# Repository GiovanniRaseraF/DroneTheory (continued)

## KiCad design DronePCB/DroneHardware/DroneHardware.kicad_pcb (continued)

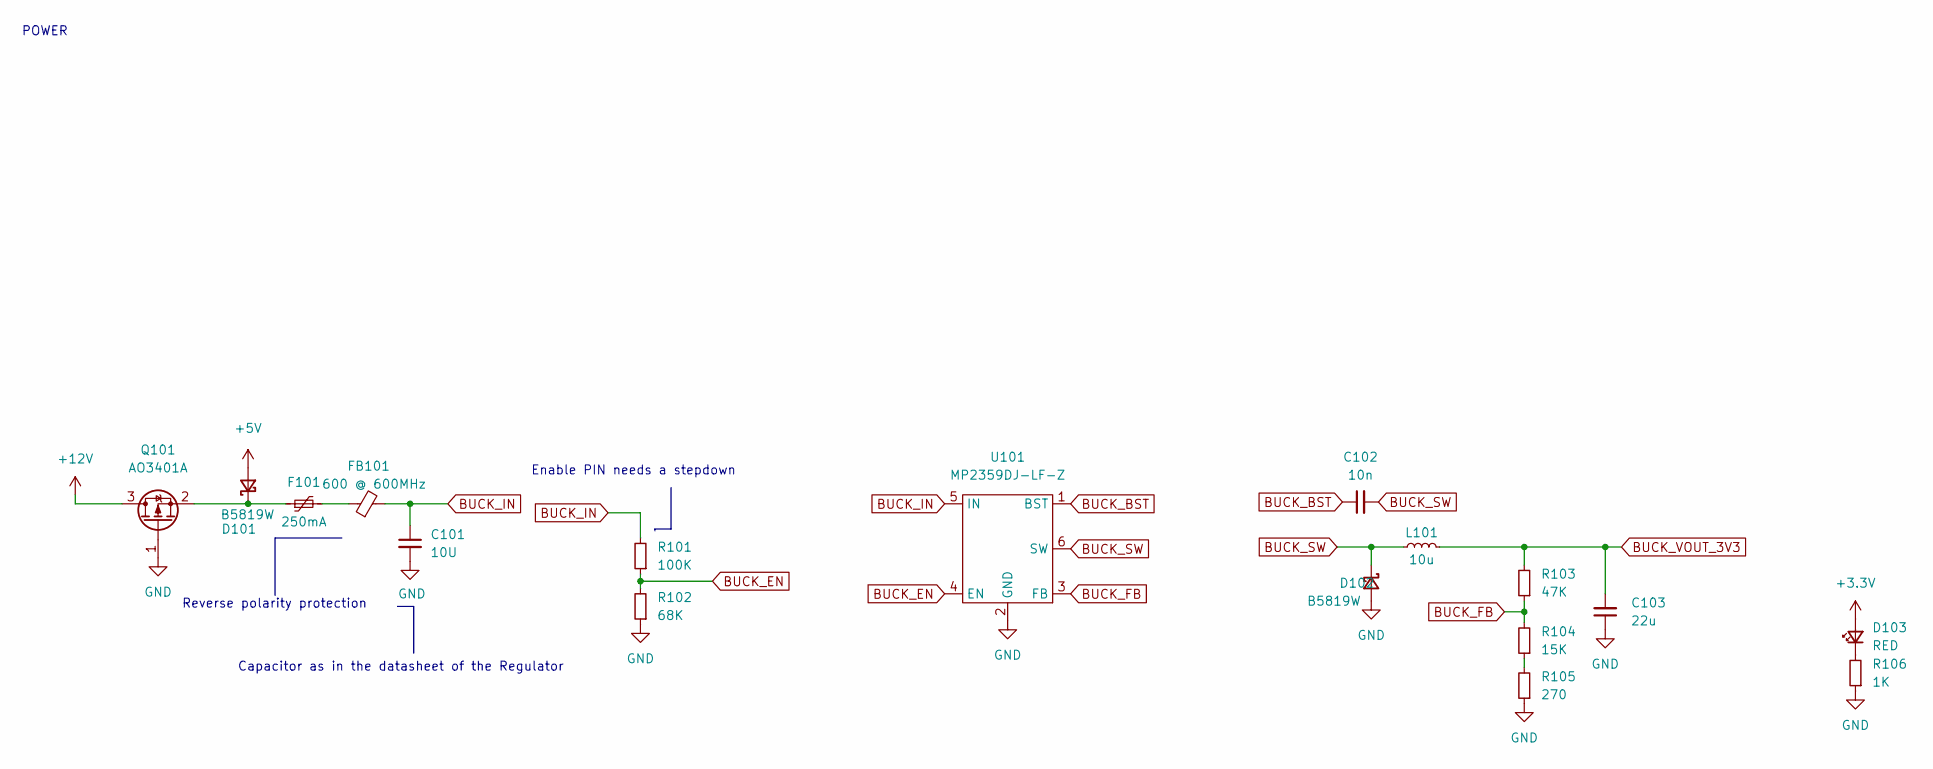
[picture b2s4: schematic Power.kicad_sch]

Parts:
C101: 10U; C_1206_3216Metric; LCSC Part # C13585
C102: 10n; C_0603_1608Metric; LCSC Part # C57112
C103: 22u; C_1206_3216Metric; LCSC Part # C12891
D101, D102: B5819W; D_SOD-123; LCSC Part # C8598
D103: RED; LED_0603_1608Metric; LCSC Part # C2286
F101: 250mA; Fuse_0603_1608Metric; LCSC Part # C151137
FB101: 600 @ 600MHz; L_0805_2012Metric; LCSC Part # C1017
L101: 10u; L_Sunlord_MWSA0518_5.4x5.2mm; LCSC Part # C139506
Q101: AO3401A; SOT-23; LCSC Part # C15127
R101: 100K; R_0603_1608Metric; LCSC Part # C25803
R102: 68K; R_0603_1608Metric; LCSC Part # C23231
R103: 47K; R_0603_1608Metric; LCSC Part # C25819
R104: 15K; R_0603_1608Metric; LCSC Part # C22809
R105: 270; R_0603_1608Metric; LCSC Part # C22966
R106: 1K; R_0603_1608Metric; LCSC Part # C21190
U101: MP2359DJ-LF-Z; SOT-23-6; LCSC Part # C14259

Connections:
+5V: D101.2 (A); also elsewhere on the board
+12V: Q101.3 (D); also elsewhere on the board
BUCK_BST: C102.1, U101.1 (BST)
BUCK_EN: R101.1, R102.2, U101.4 (EN)
BUCK_FB: R103.1, R104.2, U101.3 (FB)
BUCK_IN: C101.1, FB101.2, R101.2, U101.5 (IN)
BUCK_SW: C102.2, D102.1 (K), L101.1, U101.6 (SW)
BUCK_VOUT_3V3: C103.2, D103.2 (A), L101.2, R103.2; also elsewhere on the board
GND: C101.2, C103.1, D102.2 (A), Q101.1 (G), R102.1, R105.1, R106.1, U101.2 (GND); also elsewhere on the board
unnamed: D101.1 (K), F101.1, Q101.2 (S)
unnamed: D103.1 (K), R106.2
unnamed: F101.2, FB101.1
unnamed: R104.1, R105.2

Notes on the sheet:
Reverse polarity protection
POWER
Enable PIN needs a stepdown
Capacitor as in the datasheet of the Regulator

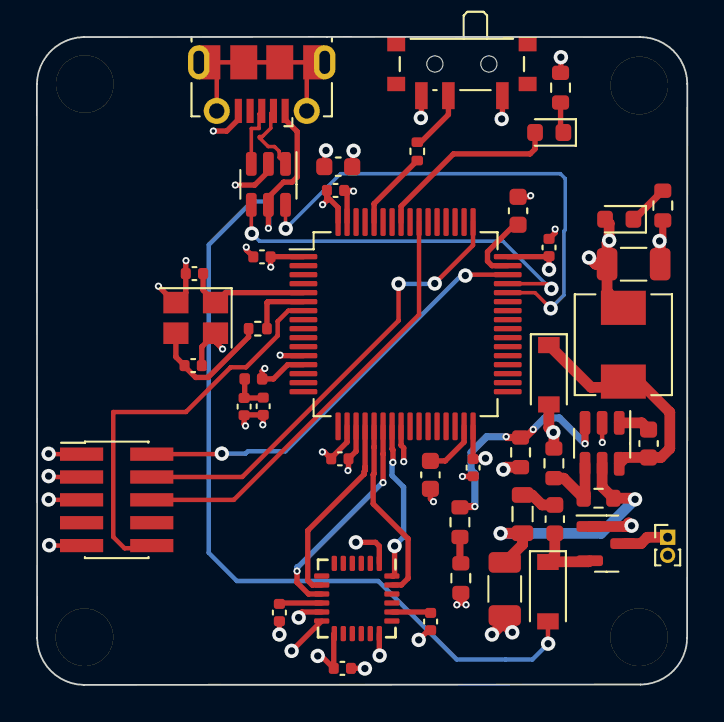
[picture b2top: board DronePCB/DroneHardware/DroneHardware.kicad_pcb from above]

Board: 6 copper layers, 36.1 x 36.0 mm, 49 parts (0 on the bottom side), 38 nets.

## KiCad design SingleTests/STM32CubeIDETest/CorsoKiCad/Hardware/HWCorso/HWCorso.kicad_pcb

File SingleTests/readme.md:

# Test dei singoli componenti Harware e Software

## CMakeOnSTM32
- E' stata creato un file cmake che permette di compilare i file di stm32
- Tutto viene integrato con un file make che permette di scaricare la toolchain per arm
- Per ora funziona su macOS e LinuxWSL 

## CodeStyleTest
- Test relativi al code style
- Utilizzo del comando astyle

## CPPArmCompilationTest
- Test di compilazione arm tramite file cmake
### Scoperte
- Deve essere creato un file cmake che funzioni diversamente e che sia più facile
- E' stato usato quello presente in CMakeOnSTM32

## STM32CubeIDETest
- Vengono eseguiti i test di compilazione tramite una generica toolchain allinterno di sistemi operativi windows e mac
### Scoperte
- Su macOS la compilazione tramite la toolchain arm funziona usando il file make che genera STM32CubeIDE
    - Da sistemare il fatto che il file make deve prendere un path generico perché in questo momento prendere un path assoluto ai file da compilare
- Su windows non è possibile compilare direttamente utilizzando il file make siccome la toolchain non ha i riferimenti giusti alla cartella
- Da testare la compilazione su linux

## CITest
- Test relativi a CI 
  
## ToolChainDownloadTest
- Bisogna sistemare il download della giusta toolchain per linux
    - Impossibile utilizzare la toolchain siccome non è compatibile con x86 
    - Sistemare l'URL di download
    - Togliere la funzione di salvataggio del file tar nella cartella utente/.env
    - Aggiungere la possibilità di sceglire il path dove estrarre la toolchain

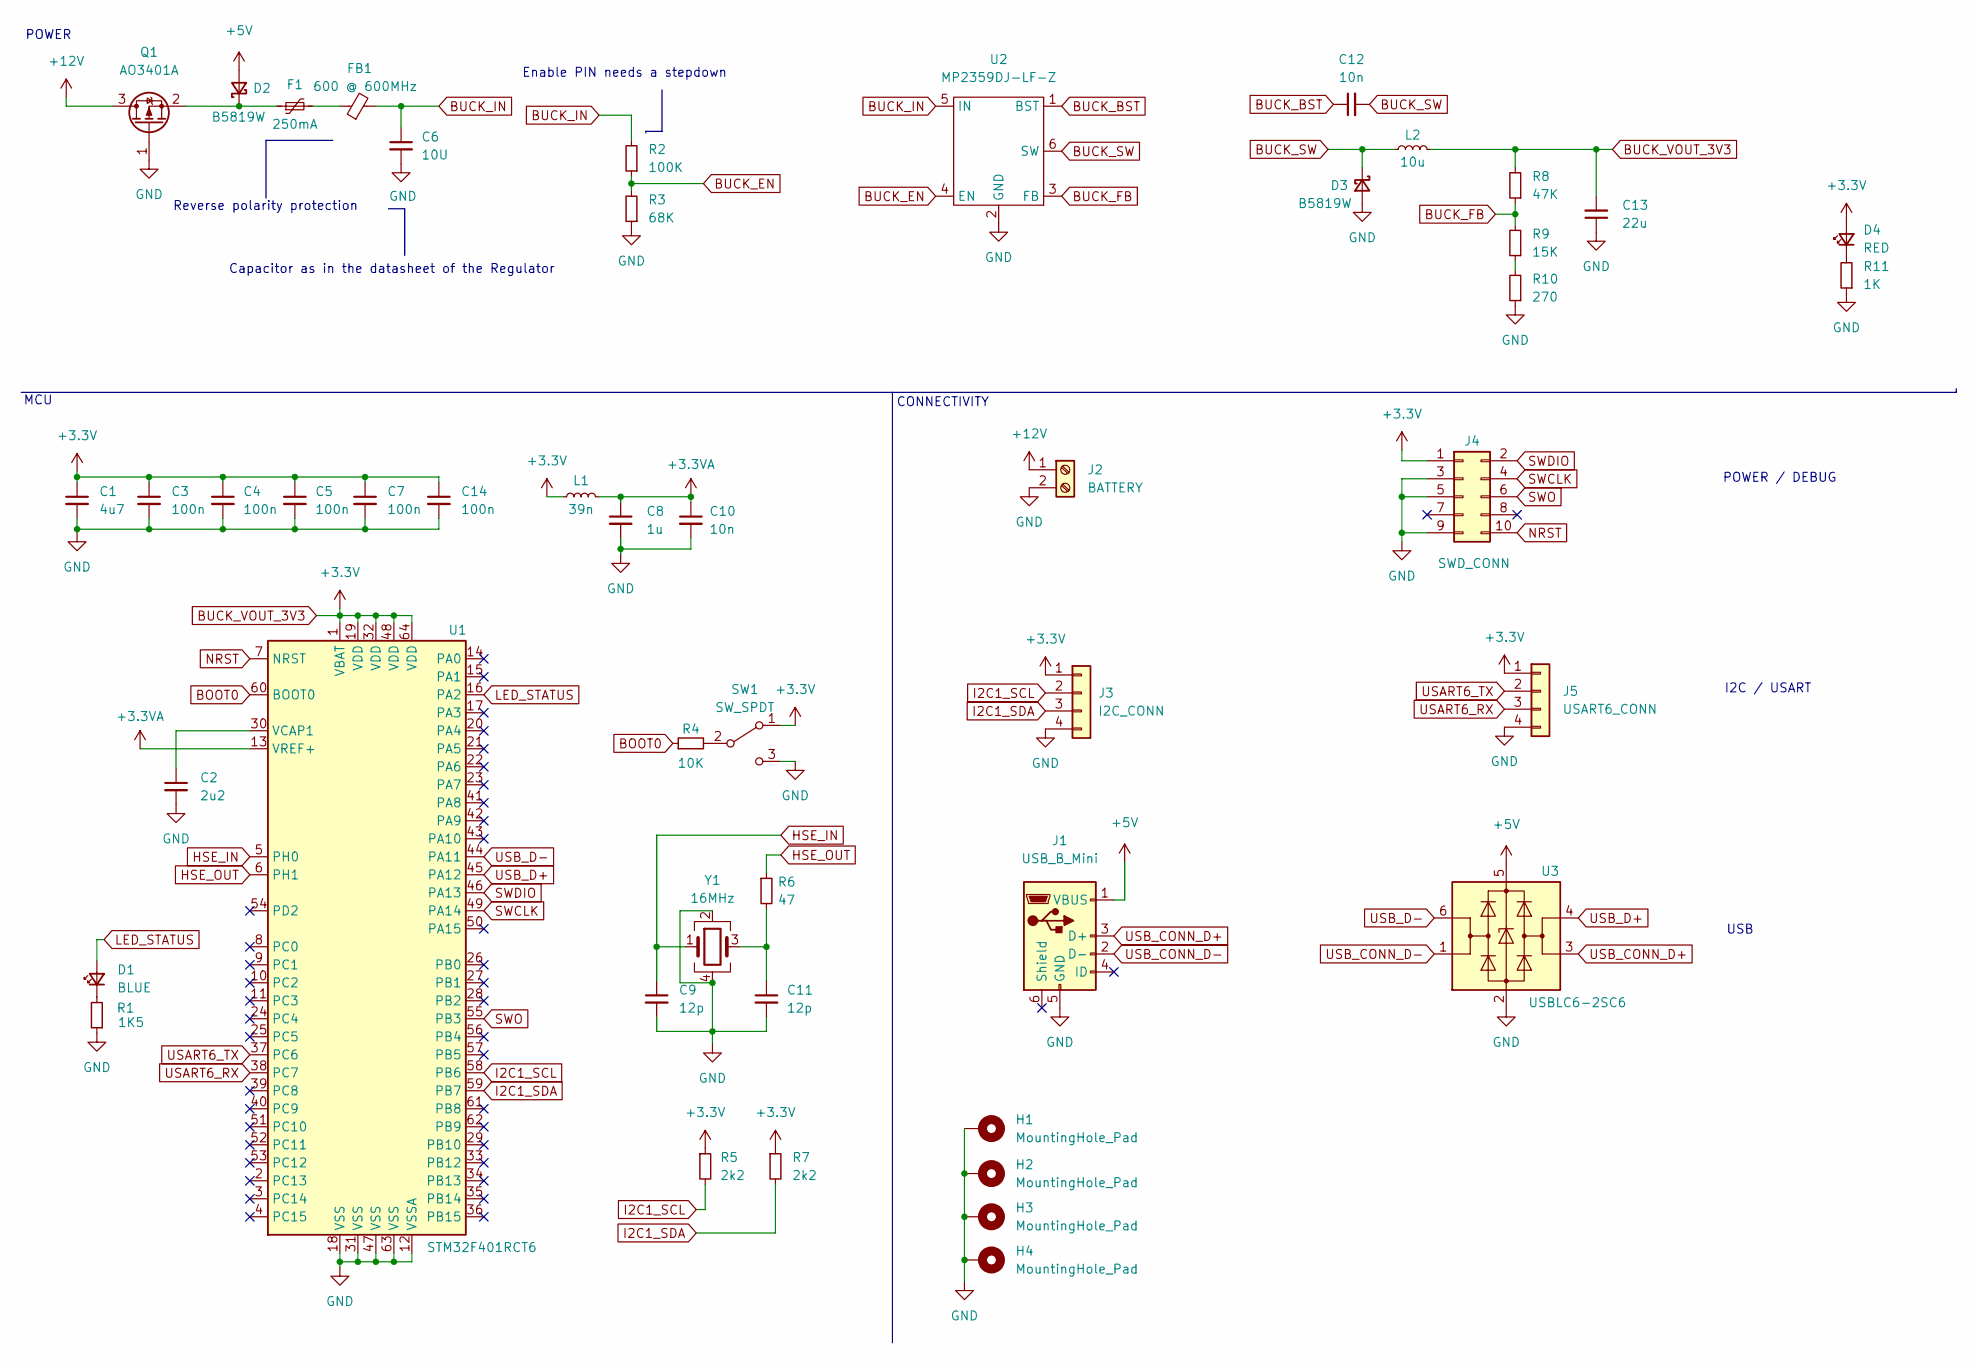
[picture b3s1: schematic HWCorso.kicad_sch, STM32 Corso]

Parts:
C1: 4u7; C_0603_1608Metric; LCSC Part # C19666
C2: 2u2; C_0603_1608Metric; LCSC Part # C23630
C3, C4, C5, C7, C14: 100n; C_0402_1005Metric; LCSC Part # C307331
C6: 10U; C_1206_3216Metric; LCSC Part # C13585
C8: 1u; C_0402_1005Metric; LCSC Part # C52923
C9, C11: 12p; C_0402_1005Metric; LCSC Part # C1547
C10: 10n; C_0402_1005Metric; LCSC Part # C15195
C12: 10n; C_0603_1608Metric; LCSC Part # C57112
C13: 22u; C_1206_3216Metric; LCSC Part # C12891
D1: BLUE; LED_0603_1608Metric; LCSC Part # C72041
D2, D3: B5819W; D_SOD-123; LCSC Part # C8598
D4: RED; LED_0603_1608Metric; LCSC Part # C2286
F1: 250mA; Fuse_0603_1608Metric; LCSC Part # C151137
FB1: 600 @ 600MHz; L_0805_2012Metric; LCSC Part # C1017
H1, H2, H3, H4: MountingHole_Pad; MountingHole_4.3mm_M4_Pad_Via
J1: USB_B_Mini; USB_Mini-B_Wuerth_65100516121_Horizontal
J2: BATTERY; TerminalBlock_Phoenix_PT-1,5-2-3.5-H_1x02_P3.50mm_Horizontal
J3: I2C_CONN; Molex_PicoBlade_53048-0410_1x04_P1.25mm_Horizontal
J4: SWD_CONN; PinHeader_2x05_P1.27mm_Vertical_SMD
J5: USART6_CONN; Molex_PicoBlade_53048-0410_1x04_P1.25mm_Horizontal
L1: 39n; L_0402_1005Metric; LCSC Part # C26443
L2: 10u; L_Sunlord_MWSA0518_5.4x5.2mm; LCSC Part # C139506
Q1: AO3401A; SOT-23; LCSC Part # C15127
R1: 1K5; R_0603_1608Metric; LCSC Part # C22843
R2: 100K; R_0603_1608Metric; LCSC Part # C25803
R3: 68K; R_0603_1608Metric; LCSC Part # C23231
R4: 10K; R_0402_1005Metric; LCSC Part # C25744
R5, R7: 2k2; R_0603_1608Metric; LCSC Part # C4190
R6: 47; R_0402_1005Metric; LCSC Part # C25792
R8: 47K; R_0603_1608Metric; LCSC Part # C25819
R9: 15K; R_0603_1608Metric; LCSC Part # C22809
R10: 270; R_0603_1608Metric; LCSC Part # C22966
R11: 1K; R_0603_1608Metric; LCSC Part # C21190
SW1: SW_SPDT; SW_SPDT_PCM12
U1: STM32F401RCT6; LQFP-64_10x10mm_P0.5mm; LCSC Part # C74524
U2: MP2359DJ-LF-Z; SOT-23-6; LCSC Part # C14259
U3: USBLC6-2SC6; SOT-23-6; LCSC Part # C2827654
Y1: 16MHz; Crystal_SMD_3225-4Pin_3.2x2.5mm; LCSC Part # C13738

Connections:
+3.3VA: C8.1, C10.1, L1.2, U1.13 (VREF+)
+5V: D2.2 (A), J1.1 (VBUS), U3.5 (VBUS)
+12V: J2.1, Q1.3 (D)
BOOT0: R4.1, U1.60 (BOOT0)
BUCK_BST: C12.1, U2.1 (BST)
BUCK_EN: R2.1, R3.2, U2.4 (EN)
BUCK_FB: R8.1, R9.2, U2.3 (FB)
BUCK_IN: C6.1, FB1.2, R2.2, U2.5 (IN)
BUCK_SW: C12.2, D3.1 (K), L2.1, U2.6 (SW)
BUCK_VOUT_3V3: C1.1, C3.1, C4.1, C5.1, C7.1, C13.2, C14.1, D4.2 (A), J3.1, J4.1, J5.1, L1.1, L2.2, R5.1, R7.1, R8.2, SW1.1 (A), U1.1 (VBAT), U1.19 (VDD), U1.32 (VDD), U1.48 (VDD), U1.64 (VDD)
GND: C1.2, C2.2, C3.2, C4.2, C5.2, C6.2, C7.2, C8.2, C9.2, C10.2, C11.2, C13.1, C14.2, D3.2 (A), H1.1, H2.1, H3.1, H4.1, J1.5 (GND), J2.2, J3.4, J4.3, J4.5, J4.9, J5.4, Q1.1 (G), R1.1, R3.1, R10.1, R11.1, SW1.3 (C), U1.12 (VSSA), U1.18 (VSS), U1.31 (VSS), U1.47 (VSS), U1.63 (VSS), U2.2 (GND), U3.2 (GND), Y1.2, Y1.4
HSE_IN: C9.1, U1.5 (PH0), Y1.1
HSE_OUT: R6.1, U1.6 (PH1)
I2C1_SCL: J3.2, R5.2, U1.58 (PB6)
I2C1_SDA: J3.3, R7.2, U1.59 (PB7)
LED_STATUS: D1.2 (A), U1.16 (PA2)
NRST: J4.10, U1.7 (NRST)
unnamed: C2.1, U1.30 (VCAP1)
unnamed: C11.1, R6.2, Y1.3
unnamed: D1.1 (K), R1.2
unnamed: D2.1 (K), F1.1, Q1.2 (S)
unnamed: D4.1 (K), R11.2
unnamed: F1.2, FB1.1
unnamed: R4.2, SW1.2 (B)
unnamed: R9.1, R10.2
SWCLK: J4.4, U1.49 (PA14)
SWDIO: J4.2, U1.46 (PA13)
SWO: J4.6, U1.55 (PB3)
USART6_RX: J5.3, U1.38 (PC7)
USART6_TX: J5.2, U1.37 (PC6)
USB_CONN_D+: J1.3 (D+), U3.3 (I/O2)
USB_CONN_D-: J1.2 (D-), U3.1 (I/O1)
USB_D+: U1.45 (PA12), U3.4 (I/O2)
USB_D-: U1.44 (PA11), U3.6 (I/O1)

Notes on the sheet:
USB
POWER
MCU
Capacitor as in the datasheet of the Regulator
I2C / USART
Enable PIN needs a stepdown
CONNECTIVITY
Reverse polarity protection
POWER / DEBUG

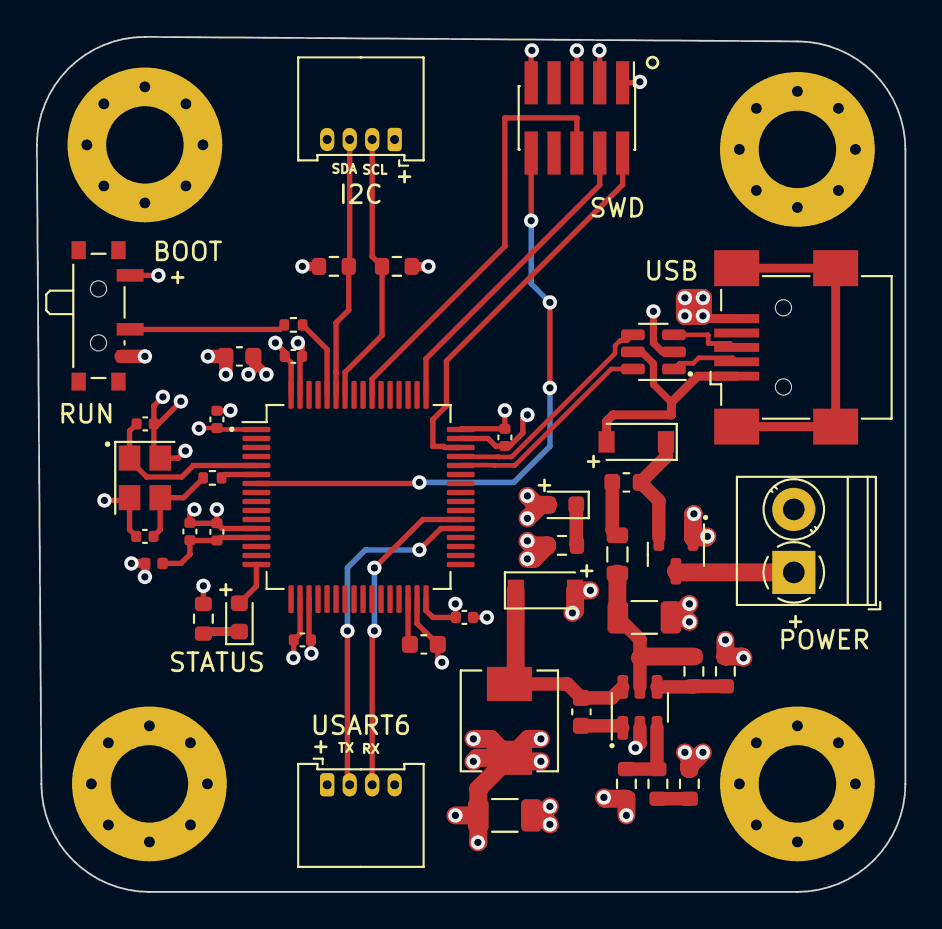
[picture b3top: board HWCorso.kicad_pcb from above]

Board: 4 copper layers, 48.2 x 47.5 mm, 48 parts (0 on the bottom side), 34 nets.

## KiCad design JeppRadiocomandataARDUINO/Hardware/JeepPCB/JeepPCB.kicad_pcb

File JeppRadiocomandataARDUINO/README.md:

# Jeep Radiocomandata
## Componenti
- Arduino Nano, ATmega328P (Old Bootloader)
- L298N Modulo, ESC per motori CC, [DataScheet](https://www.st.com/resource/en/datasheet/l298.pdf)
- Radio FlySky
- Ricevente FlySky FS-A8S
- Motori 10V CC
- Cavo usb mini per il flashing
- Tester
- Batteria 4S a 14V

## Software 
- Arduino IDE o equivalenti

## Schematica
- file: [Schematica](./Schematica.jpeg)

## Canali
```c
// PPM Channels
const byte rightStick_LeftRight = 1;
const byte rightStick_UpDown    = 2;
const byte leftStick_UpDown     = 3;
const byte leftStick_LeftRight  = 4;
const byte VRA                  = 5;
const byte VRB                  = 6;
```

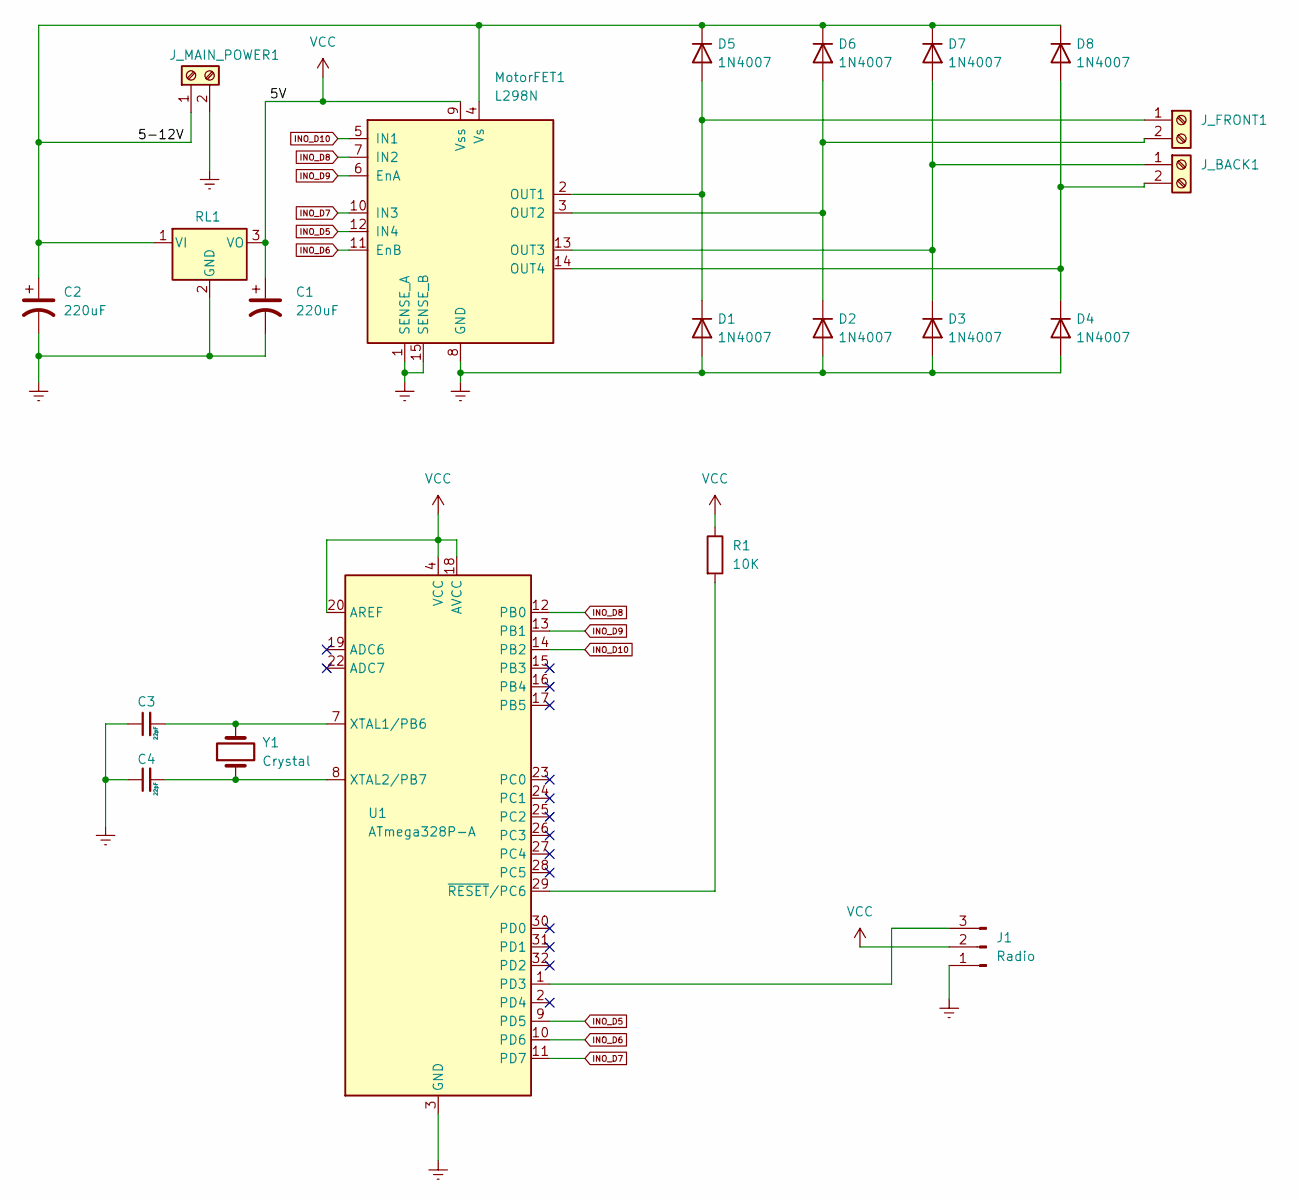
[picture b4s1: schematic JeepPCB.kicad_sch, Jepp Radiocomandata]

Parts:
C1, C2: 220uF; C_Elec_8x10.2
C3, C4: 22pF; CP_EIA-1608-10_AVX-L_Pad1.25x1.05mm_HandSolder
D1, D2, D3, D4, D5, D6, D7, D8: 1N4007; D_MicroMELF_Handsoldering
J1: Radio; PinHeader_1x03_P2.00mm_Vertical
J_BACK1: Screw_Terminal_01x02; TerminalBlock_Phoenix_MKDS-1,5-2-5.08_1x02_P5.08mm_Horizont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
J_FRONT1: Screw_Terminal_01x02; TerminalBlock_Phoenix_MKDS-1,5-2-5.08_1x02_P5.08mm_Horizont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
J_MAIN_POWER1: Screw_Terminal_01x02; TerminalBlock_Phoenix_MKDS-1,5-2-5.08_1x02_P5.08mm_Horizont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
MotorFET1: L298N; TO-220-15_P2.54x2.54mm_StaggerOdd_Lead4.58mm_Vertical
R1: 10K; R_0402_1005Metric
RL1: KA78M05_TO252; TO-252-2
U1: ATmega328P-A; TQFP-32_7x7mm_P0.8mm
Y1: Crystal; Crystal_SMD_0603-2Pin_6.0x3.5mm

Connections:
/5-12V: C2.1, D5.1 (K), D6.1 (K), D7.1 (K), D8.1 (K), J_MAIN_POWER1.1, MotorFET1.4 (Vs), RL1.1 (VI)
Earth: C1.2, C2.2, C3.1, C4.1, D1.2 (A), D2.2 (A), D3.2 (A), D4.2 (A), J1.1, J_MAIN_POWER1.2, MotorFET1.1 (SENSE_A), MotorFET1.8 (GND), MotorFET1.15 (SENSE_B), RL1.2 (GND), U1.3 (GND), U1.5 (GND), U1.21 (GND)
INO_D5: MotorFET1.12 (IN4), U1.9 (PD5)
INO_D6: MotorFET1.11 (EnB), U1.10 (PD6)
INO_D7: MotorFET1.10 (IN3), U1.11 (PD7)
INO_D8: MotorFET1.7 (IN2), U1.12 (PB0)
INO_D9: MotorFET1.6 (EnA), U1.13 (PB1)
INO_D10: MotorFET1.5 (IN1), U1.14 (PB2)
unnamed: C3.2, U1.7 (XTAL1/PB6), Y1.2
unnamed: C4.2, U1.8 (XTAL2/PB7), Y1.1
unnamed: D1.1 (K), D5.2 (A), J_FRONT1.1, MotorFET1.2 (OUT1)
unnamed: D2.1 (K), D6.2 (A), J_FRONT1.2, MotorFET1.3 (OUT2)
unnamed: D3.1 (K), D7.2 (A), J_BACK1.1, MotorFET1.13 (OUT3)
unnamed: D4.1 (K), D8.2 (A), J_BACK1.2, MotorFET1.14 (OUT4)
unnamed: J1.3, U1.1 (PD3)
unnamed: R1.2, U1.29 (~RESET/PC6)
VCC: C1.1, J1.2, MotorFET1.9 (Vss), R1.1, RL1.3 (VO), U1.4 (VCC), U1.6 (VCC), U1.18 (AVCC), U1.20 (AREF)

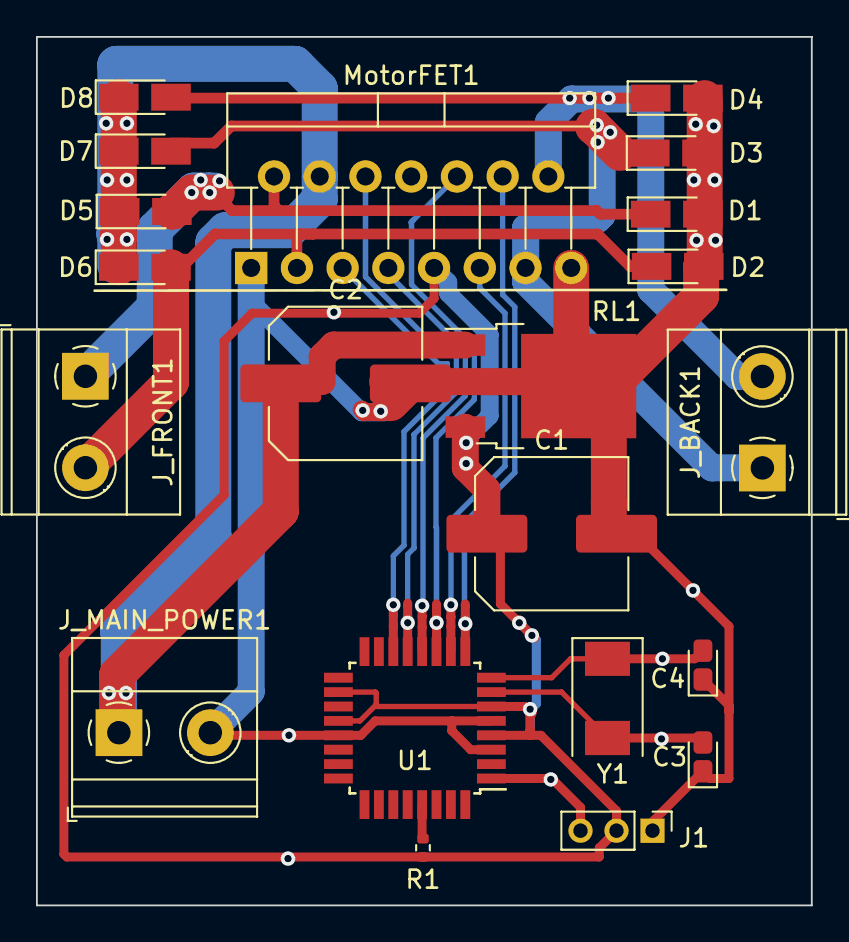
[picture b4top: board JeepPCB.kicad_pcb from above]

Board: 2 copper layers, 43.0 x 48.2 mm, 21 parts (0 on the bottom side), 17 nets.

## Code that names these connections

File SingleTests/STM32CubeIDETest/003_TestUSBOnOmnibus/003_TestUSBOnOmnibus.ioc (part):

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Mcu.Name=STM32F405RGTx
Mcu.Package=LQFP64
Mcu.UserName=STM32F405RGTx
PA10.Mode=Asynchronous
PA10.Signal=USART1_RX
PA13.Mode=Serial_Wire
PA13.Signal=SYS_JTMS-SWDIO
PA14.Mode=Serial_Wire
PA14.Signal=SYS_JTCK-SWCLK
PA2.Mode=Asynchronous
PA2.Signal=USART2_TX
PA3.Mode=Asynchronous
PA3.Signal=USART2_RX
PA9.Mode=Asynchronous
PA9.Signal=USART1_TX
PB10.Mode=Asynchronous
PB10.Signal=USART3_TX
PB11.Mode=Asynchronous
PB11.Signal=USART3_RX
PB5.GPIOParameters=GPIO_Label
PB5.GPIO_Label=LED_State
PB5.Signal=GPIO_Output
PC14-OSC32_IN.Mode=LSE-External-Oscillator
PC14-OSC32_IN.Signal=RCC_OSC32_IN
PC15-OSC32_OUT.Mode=LSE-External-Oscillator
PC15-OSC32_OUT.Signal=RCC_OSC32_OUT
PC6.Mode=Asynchronous
PC6.Signal=USART6_TX
PC7.Mode=Asynchronous
PC7.Signal=USART6_RX
PH0-OSC_IN.Mode=HSE-External-Oscillator
PH0-OSC_IN.Signal=RCC_OSC_IN
PH1-OSC_OUT.Mode=HSE-External-Oscillator
PH1-OSC_OUT.Signal=RCC_OSC_OUT
RCC.HSE_VALUE=16000000
RCC.SYSCLKFreq_VALUE=168000000
RCC.SYSCLKSource=RCC_SYSCLKSOURCE_PLLCLK
board=custom

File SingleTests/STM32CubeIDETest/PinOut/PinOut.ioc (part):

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Mcu.Name=STM32F405RGTx
Mcu.Package=LQFP64
Mcu.UserName=STM32F405RGTx
PA10.Mode=Asynchronous
PA10.Signal=USART1_RX
PA5.Mode=Full_Duplex_Master
PA5.Signal=SPI1_SCK
PA6.Mode=Full_Duplex_Master
PA6.Signal=SPI1_MISO
PA7.Mode=Full_Duplex_Master
PA7.Signal=SPI1_MOSI
PA9.Mode=Asynchronous
PA9.Signal=USART1_TX
PB10.Mode=Asynchronous
PB10.Signal=USART3_TX
PB11.Mode=Asynchronous
PB11.Signal=USART3_RX
PC6.Mode=Synchronous
PC6.Signal=USART6_TX
PC7.Mode=Synchronous
PC7.Signal=USART6_RX
PC8.Mode=Synchronous
PC8.Signal=USART6_CK
RCC.HSE_VALUE=25000000
RCC.SYSCLKFreq_VALUE=16000000
board=custom

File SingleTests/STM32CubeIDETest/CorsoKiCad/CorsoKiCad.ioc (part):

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Mcu.Name=STM32F401R(B-C)Tx
Mcu.Package=LQFP64
Mcu.UserName=STM32F401RCTx
PA11.Mode=Device_Only
PA11.Signal=USB_OTG_FS_DM
PA12.Mode=Device_Only
PA12.Signal=USB_OTG_FS_DP
PA13.Mode=Trace_Asynchronous_SW
PA13.Signal=SYS_JTMS-SWDIO
PA14.Mode=Trace_Asynchronous_SW
PA14.Signal=SYS_JTCK-SWCLK
PA8.Mode=I2C
PA8.Signal=I2C3_SCL
PB3.Mode=Trace_Asynchronous_SW
PB3.Signal=SYS_JTDO-SWO
PB6.Mode=I2C
PB6.Signal=I2C1_SCL
PB7.Mode=I2C
PB7.Signal=I2C1_SDA
PC6.Mode=Asynchronous
PC6.Signal=USART6_TX
PC7.Mode=Asynchronous
PC7.Signal=USART6_RX
PC9.Mode=I2C
PC9.Signal=I2C3_SDA
PH0\ -\ OSC_IN.Mode=HSE-External-Oscillator
PH0\ -\ OSC_IN.Signal=RCC_OSC_IN
PH1\ -\ OSC_OUT.Mode=HSE-External-Oscillator
PH1\ -\ OSC_OUT.Signal=RCC_OSC_OUT
RCC.HSE_VALUE=25000000
RCC.SYSCLKFreq_VALUE=16000000
board=custom

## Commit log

2022-05-27 Init
    Creazione del file di progetto
2022-05-27 Init
    Test di funzionamento
2022-05-27 Creazione del file dei requisiti del progetto
2022-05-27 Adding Coding Style
2022-05-27 Aggiunta dei documenti
2022-05-27 Aggiornamento Idee e Test
    Creazione delle cartelle per i test e descrizione dei test singoli
2022-05-27 Errori di ortografia
2022-05-27 Test di STM32CubeIDE
2022-05-27 Aggiunta test della toolchain
2022-05-27 Aggiunto del tast di modifica dello Script di download della toolchain
2022-05-27 Ho provato a vedere se funzionano i pull request
2022-05-28 Test di compilazione su MacOS
2022-05-28 Aggiunta del lavoro sul file di download.sh
2022-05-28 Creazione del diagramma delle cose da implementare
2022-05-28 Correzione Italiano
2022-05-28 Correzione
2022-05-28 Aggiornamento del Gantt
2022-05-29 Download della toolchain
    Funziona il download di una versione specifica
2022-05-30 Aggiornamento Gantt
2022-05-30 Aggiunta delle compilazione di un file generico
2022-05-30 Aggiornamento del file di download.sh
    Adesso è possibile scaricare la toolchain anche su macOS
    ISSUE: https://github.com/GiovanniRaseraF/DroneTheory/issues/5
2022-05-31 Test di CMake
    Sono stati fatti dei test per capire come viene compilato inav tramite CMake
2022-05-31 Test di CMake
2022-05-31 Compilazione tramite cmake
2022-05-31 Test di cmake funzionante
2022-05-31 Aggiunta dei file di makefile
2022-05-31 Test su Windows
2022-05-31 Aggiunta del download della toolchain adatta
2022-05-31 Correzione del nome del file
2022-05-31 Aggiornamento del make in modo da eseguire il download
2022-06-01 Test di generazione di un segnale PWM
2022-06-01 Pulizia della cartella di test
2022-06-02 Test di scrittura su porta seriale
2022-06-02 Test di astyle
2022-06-02 Test di invio e ricezione attraverso porta UART2
2022-06-02 Ulteriori Test di comunicazione UART
2022-06-03 Test di UART con iterrupt
    Il prossimo passo è leggere UART utilizzando DMA
2022-06-04 Aggiornamento e test di UART e comunicazione con console printf()
2022-06-06 Test
2022-06-06 Aggiunta di un link utile
2022-06-07 Output PWM su stm32
2022-06-08 Lettura gyro da stm32
2022-06-08 Test di lettura della ricevente da arduino
2022-06-09 Test radio
2022-06-09 Test di IBUS su STM32
2022-06-09 Link per il collegamento di ricevente a betaflight
2022-06-10 Lettura del segnale PPM dalla radio
2022-06-10 Lettura e scrittura del segnale PPM nei motori
2022-06-11 Aggiunta della foto del pacchetto PPM
2022-06-11 Foto della Scheda elettronica della jeep Radiocomandata
2022-06-13 Jepp radiocomandata costruita
2022-06-13 Codice jeep radiocomandata
2022-06-14 Jeep Programmata
2022-06-14 Formattazione
2022-06-14 Aggiunta Schematica e README
2022-06-14 Implementazione della retro
2022-06-14 Aggiunta dei canali PPM
2022-06-14 Canali PPM
2022-06-15 Scrittura di SimplePPM
2022-06-16 Implementazione della macchina a stati per lettura di PPM
2022-06-16 Lettura della radio PPM con interrupt
2022-06-16 SimplePPM implementation
2022-06-16 Aggiornamento della jeep ppm
2022-06-17 Inizio di SPPM Smoother
2022-06-17 Creazione del PCB della Jeep Radiocomandata
2022-06-18 Modello del PCB della Jeep iniziato
2022-06-20 Creazione del PCB personalizzato
    Design in KiCad e rimozione delle componenti necessarie
2022-06-20 Modello 3D del FET
2022-06-20 Aggiunta della CPU ATmega328P
2022-06-21 Aggiornamento del PCB
2022-06-21 Aggiornamento PCB Jeep
    Aggiunta delle connessioni necessarie per il processore
2022-06-21 Aggiornamento della resistenza da 10K e posizionamento dei componenti
2022-06-22 Collegamento delle tracce
2022-06-23 Modifiche alla scheda
2022-06-23 Aggiornamento delle tracce
2022-06-24 Jeep Finita
2022-06-24 Test di aggiunta testpad
2022-06-26 Spostamento dei DIODI per dare più spazio alla saldatura
2022-06-27 Collegamenti di Atmega328 più chiari
2022-06-27 Script per lo stile dei file c++
2022-06-28 Aggiornamento del PCB aggiunta di VCC e di Vie
2022-06-28 Caricamento del file Gerber
2022-06-28 File gerber e file dei fori
2022-06-29 Foot Print del processore a 8 bit che verrà utilizzato al posto di ATMega328P
2022-06-30 Creazione di una scheda per il corso
2022-06-30 Aggiunta dei filtri negli input e Cristallo
2022-07-01 Creazione della scheda del flight controller
2022-07-01 Scelta componenti e creazione PCD
2022-07-01 Posizionamento dei componenti
2022-07-04 Layout della scheda
2022-07-05 Routing della scheda
2022-07-05 File BOM e traduzione del file XML in csv
2022-07-05 xml BOM parser
2022-07-05 Eliminazioni di alcuni file vecchi, aggiunta di una cartella con script utili
2022-07-05 Pulizia generale
2022-07-06 Creazione della prima versione della scheda del Drone
2022-07-06 Inizio collegamenti MPU-6000
2022-07-06 Aggiornamento Aggiunta della MPU-6050 per test
    E' stato fatto uno studio per capire il funzionamento di OMNIBUSF4
2022-07-07 Creazione PCB e utilizzo di processore STM32F405
2022-07-07 Creazione dei bordi della scheda e posizionamento dei componenti importanti
2022-07-08 Modifica della porta USB
2022-07-09 Utilizzo di mpu-6000
2022-07-09 Da eliminare
2022-07-09 Collegamento corretto di mpu-6000
2022-07-10 Collegamento fisico di MPU-6000
2022-07-10 Miglioramento delle connessioni
2022-07-10 Posizionamento di tutte le componenti
2022-07-10 Versione con input a 5V e regolatore dc-dc lm3940
2022-07-11 Creazione della scheda con il convertitore da 5V a 3.3V
2022-07-11 Test per lo spostamento della porta usb
2022-07-11 Aggiunta dei segnali PWM
2022-07-12 Collegamento di USB con resistenze da 22Ohm
2022-07-12 Collegamento USB con resistenze da 22Ohm
2022-07-12 Collegamento di dei segnali PWM dei motori
2022-07-14 Hardware della jeep arrivato
2022-07-15 Creazione della lettura del controller fake
2022-07-16 Aggiunta della reriale
2022-07-17 Prova dell'utilizzo del controller frsky
2022-07-18 Pulizia
2022-07-20 Tailless
2022-07-21 Aggiornamento delle pubblicazioni
2022-07-21 Certificato A1 + A3
2022-07-22 Aggiornamento argomenti
2022-07-23 Aggiunta delle porte USART
2022-07-23 Aggiunta di USART per RC
2022-07-25 Aggiornamento README
2022-07-26 Pulizia delle tracce
2022-07-26 Cos'é L8V
2022-07-27 Aumento dello spessore delle tracce da 5V
2022-07-30 Nuovo stack
2022-07-31 Aggiunta dell'alimentazine della radio e il GND
2022-08-01 BOM e pos file
2022-08-02 Modifica delle componenti 0201 in componenti 0402
2022-08-03 Collegamento 12V e 5V
2022-08-04 Scheda Vespin 1.0 fatta spampare
2022-08-06 Utilizzo di ArduPilot
2022-08-08 Aggiunta del file TODO
2022-08-08 Aggiunta di un TODO
2022-08-10 Testing
2022-08-11 Aggiornamento sullo studio di ArduPilot
2022-08-12 Aggiornamento dello studio di ArduPilot
2022-08-13 Lettura libro
2022-08-16 DevCall
2022-08-20 Passaggio delle Vie da 0.2 a 0.4 mm
2022-08-21 Aggiornamento delle vie da 0.2 a 0.4 mm, mancano le vie di pwm, le vie relative a MPU6000 e relative e USB
2022-08-22 Utilizzo di FreeRTOS
2022-08-22 In stampa 22 agosto 2022
2022-08-23 Aggiornamento e stampa, sbagliata di un componente
2022-08-24 Aggiunta delle aziende interessanti
2022-08-24 Aggiornamento delle possibili aziende
2022-08-25 Utilizzo di FreeRTOS per la creazione di threads
2022-08-25 Modifica
2022-08-25 Utilizzo di FreeRTOS su omnibusF4
2022-08-27 Utilizzo di USB per comunicazione serial: ESITO NEGATIVO
2022-08-27 Utilizzo di una UART per del debug di STM32F405
2022-09-08 Aggiunta dell'immagine del PCB di Vespin 1.0
2022-09-08 Test del PCB di Vespin 1.0
2022-09-09 Aggiunta del test del Clock di Vespin 1.0
2022-09-10 Test del timer
2022-09-11 Documentazione di Cortex-M4
2022-09-17 Vespin 2.0 Iniziato
2022-09-25 Aggiornamento delle componenti
2022-09-28 esp32
2022-09-29 Test Thread ESP32 e discussione con Nicola
